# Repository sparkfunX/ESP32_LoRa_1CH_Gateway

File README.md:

SparkX ESP32 LoRa Single-Channel Gateway
========================================

This repo is the original SparkX version. Please see the [SparkFun repo](https://github.com/sparkfun/ESP32_LoRa_1Ch_Gateway/) for the latest and greatest.

[*SparkX  ESP32 LoRa Single-Channel Gateway (SPX-14893)*](https://www.sparkfun.com/products/14893)

The SparkX ESP32 LoRa Single-Channel Gateway combines an ESP32 -- a programmable microcontroller featuring both WiFi and Bluetooth radios -- with an RFM95W LoRa transceiver to create a single-channel LoRa gateway. It's a perfect, low-cost tool for monitoring a dozen-or-so LoRa devices, and relaying their messages up to the cloud.

Complete with a [Qwiic connector](https://www.sparkfun.com/qwiic) and a breadboard-compatible array of ESP32 pin-breakouts, this board can can also serve as a general-purpose ESP32/RFM95W development platform. So, instead of using it as a LoRaWAN gateway, you can turn it into a **LoRa device**, and use the powerful ESP32 microcontroller to monitor sensors, host a web server, run a display or more.

These boards are a great way to begin dipping your toes into the world of LoRa and LoRaWAN. Not only can they be programmed as versatile single-channel gateway, but they can also be used as a LoRa device, or a general ESP32/RFM95W development board.

For more information, check out our [ESP32 LoRa 1-CH Gateway, LoRaWAN, and the Things Network](https://learn.sparkfun.com/tutorials/esp32-lora-1-ch-gateway-lorawan-and-the-things-network) tutorial, which explains how to set the board up, and get it connected to The Things Network.

SparkFun labored with love to create this code. Feel like supporting open source hardware? 
Buy a [breakout board](https://www.sparkfun.com/products/14893) from SparkFun!

Repository Contents
-------------------

* **/Documents** - Datasheets
* **/Hardware** - Eagle design files (.brd, .sch)
* **/Firmware** - Example code and esp32-Arduino board files

License Information
-------------------

This product is _**open source**_! 

If you have any questions or concerns on licensing, please contact techsupport@sparkfun.com.

Please use, reuse, and modify these files as you see fit. Please maintain attribution to SparkFun Electronics and release any derivative under the same license.

Distributed as-is; no warranty is given.

- Your friends at SparkFun.

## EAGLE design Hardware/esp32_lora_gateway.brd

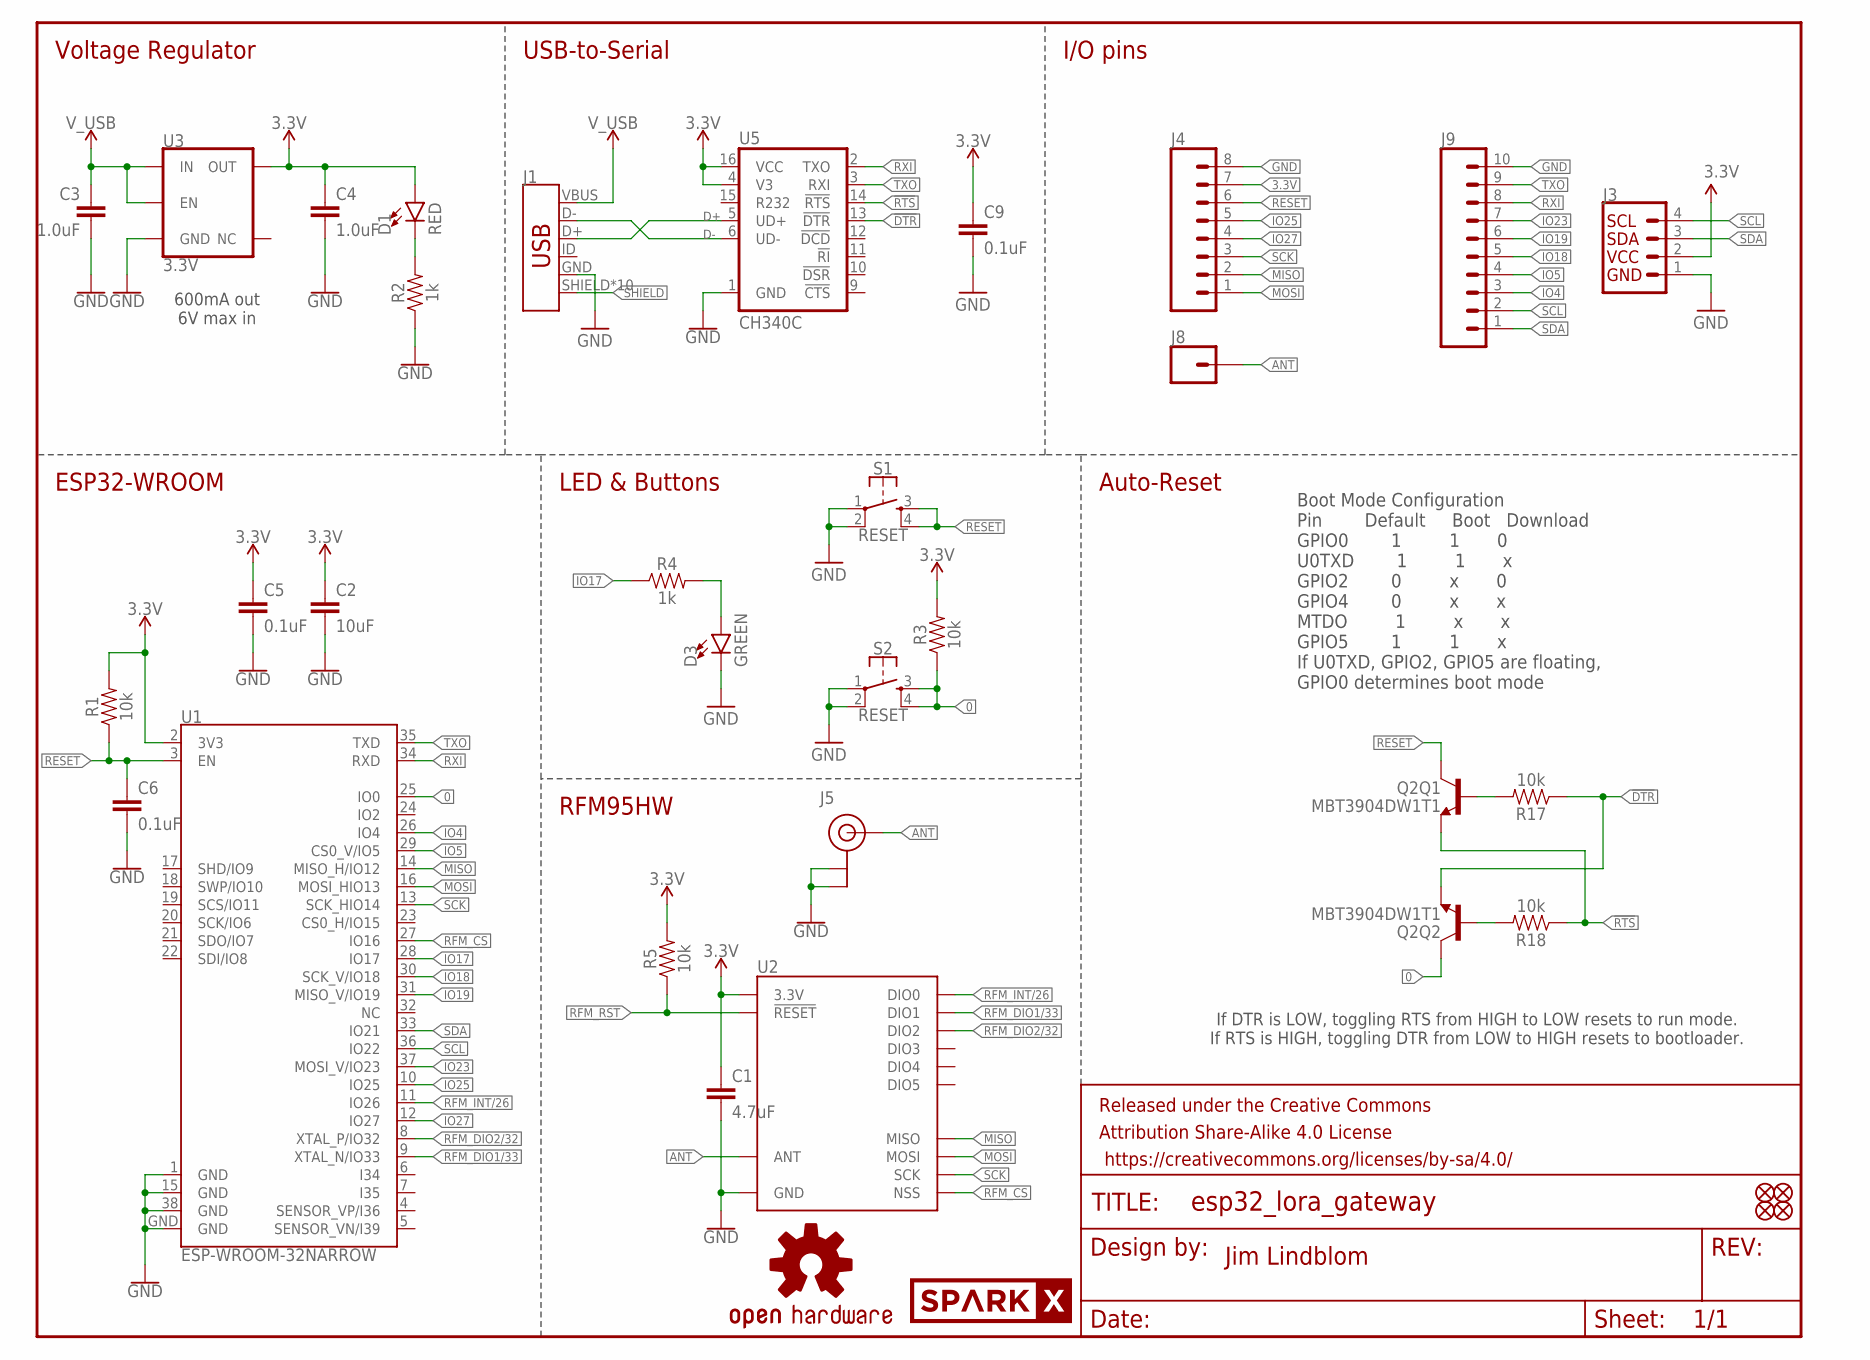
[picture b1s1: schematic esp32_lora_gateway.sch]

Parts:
C1: 4.7uF; 0603
C2: 10uF; 0603
C3, C4: 1.0uF; 0603
C5, C6: 0.1uF; 0603
C9: 0.1uF; 0603-CAP
D1: RED; LED-0603
D3: GREEN; LED-0603
FD1, FD2, FD3, FD4: FIDUCIALUFIDUCIAL; FIDUCIAL-MICRO
FRAME1: FRAME-LETTER; CREATIVE_COMMONS
J1: USB_MICRO-B_HALF_PTH_MILL; USB-MICROB-PTH-MILL
J3: QWIIC_CONNECTORJS-1MM; 1X04_1MM_RA
J4: CONN_08NO_SILK_FEMALE_PTH; 1X08_NO_SILK
J5: U.FL
J8: CONN_01PTH_NO_SILK_YES_STOP; 1X01_NO_SILK
J9: CONN_10NO_SILK_PTH_FEMALE; 1X10_NO_SILK
LOGO1: SPARKX-LOGO4; SPARKX-MEDIUM
LOGO2: OSHW-LOGOM; OSHW-LOGO-M
Q2: MBT3904DW1T1; SC70-6
R1, R3, R5, R17, R18: 10k; 0603
R2, R4: 1k; 0603
S1, S2: RESET; TACTILE_SWITCH_SMD_4.6X2.8MM
U1: ESP-WROOM-32NARROW; ESP-WROOM-32-NARROW
U2: RFM96W; RFM95/96/97/98W
U3: 3.3V; SOT23-5
U5: CH340C; SO016

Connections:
0: Q2.6 (C), R3.1, S2.3, S2.4, U1.25 (IO0)
3.3V: C1.1, C2.1, C4.1, C5.1, C9.1, D1.A, J3.2, J4.7, R1.2, R3.2, R5.2, U1.2 (3V3), U2.3.3V, U3.5 (OUT), U5.4 (V3), U5.16 (VCC)
!DTR: Q2.1 (E), R17.1, U5.13 (!DTR)
!RTS: Q2.4 (E), R18.1, U5.14 (!RTS)
ANT: J5.FEED (SIGNAL), J8.1, U2.ANT
D+: J1.D+, U5.5 (UD+)
D-: J1.D-, U5.6 (UD-)
GND: C1.2, C2.2, C3.2, C4.2, C5.2, C6.2, C9.2, D3.C, J1.GND, J3.1, J4.8, J5.1 (GND), J5.2 (GND), J9.10, R2.1, S1.1, S1.2, S2.1, S2.2, U1.1 (GND), U1.15 (GND), U1.38 (GND), U1.GND, U2.GND@1 (GND), U2.GND@2 (GND), U2.GND@3 (GND), U3.2 (GND), U5.1 (GND)
IO4: J9.3, U1.26 (IO4)
IO5: J9.4, U1.29 (CS0_V/IO5)
IO17: R4.1, U1.28 (IO17)
IO18: J9.5, U1.30 (SCK_V/IO18)
IO19: J9.6, U1.31 (MISO_V/IO19)
IO23: J9.7, U1.37 (MOSI_V/IO23)
IO25: J4.5, U1.10 (IO25)
IO27: J4.4, U1.12 (IO27)
MISO: J4.2, U1.14 (MISO_H/IO12), U2.MISO
MOSI: J4.1, U1.16 (MOSI_HIO13), U2.MOSI
unnamed: D1.C, R2.2
unnamed: D3.A, R4.2
unnamed: Q2.5 (B), R17.2
unnamed: Q2.2 (B), R18.2
RESET: C6.1, J4.6, Q2.3 (C), R1.1, S1.3, S1.4, U1.3 (EN)
RFM_CS: U1.27 (IO16), U2.NSS
RFM_DIO1/33: U1.9 (XTAL_N/IO33), U2.DIO1
RFM_DIO2/32: U1.8 (XTAL_P/IO32), U2.DIO2
RFM_INT/26: U1.11 (IO26), U2.DIO0
RFM_RST: R5.1, U2.!RESET
RXI: J9.8, U1.34 (RXD), U5.2 (TXO)
SCK: J4.3, U1.13 (SCK_HIO14), U2.SCK
SCL: J3.4, J9.2, U1.36 (IO22)
SDA: J3.3, J9.1, U1.33 (IO21)
SHIELD: J1.SHIELD, J1.SHIELD2 (SHIELD), J1.SHIELD3 (SHIELD), J1.SHIELD4 (SHIELD), J1.SHIELD5 (SHIELD), J1.SHIELD6 (SHIELD), J1.SHIELD7 (SHIELD), J1.SHIELD8 (SHIELD), J1.SHIELD9 (SHIELD), J1.SHIELD10 (SHIELD)
TXO: J9.9, U1.35 (TXD), U5.3 (RXI)
V_USB: C3.1, J1.VBUS, U3.1 (IN), U3.3 (EN)

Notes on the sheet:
Boot Mode Configuration Pin Default Boot Download GPIO0 1 1 0 U0TXD 1 1 x GPIO2 0 x 0 GPIO4 0 x x MTDO 1 x x GPIO5 1 1 x If U0TXD, GPIO2, GPIO5 are floating, GPIO0 determines boot mode
If DTR is LOW, toggling RTS from HIGH to LOW resets to run mode. If RTS is HIGH, toggling DTR from LOW to HIGH resets to bootloader.
600mA out 6V max in
Voltage Regulator
USB-to-Serial
I/O pins
ESP32-WROOM
LED & Buttons
Auto-Reset
RFM95HW
Jim Lindblom

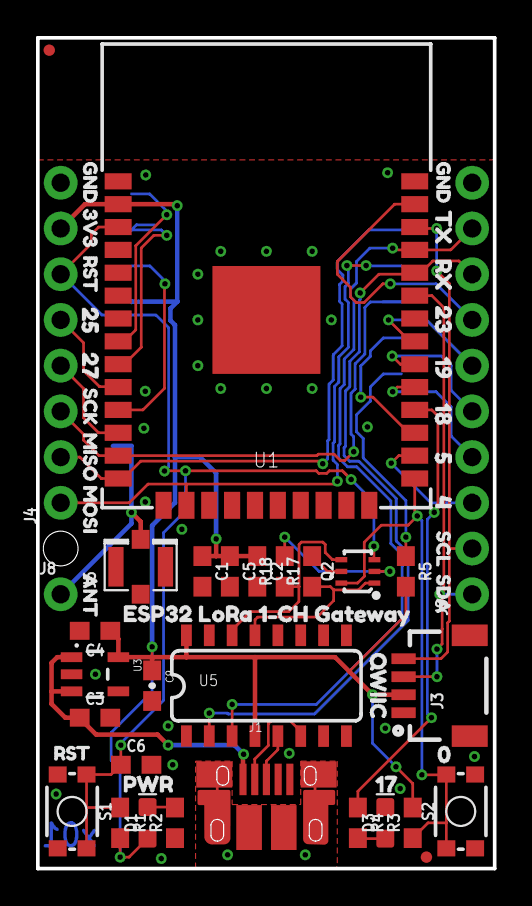
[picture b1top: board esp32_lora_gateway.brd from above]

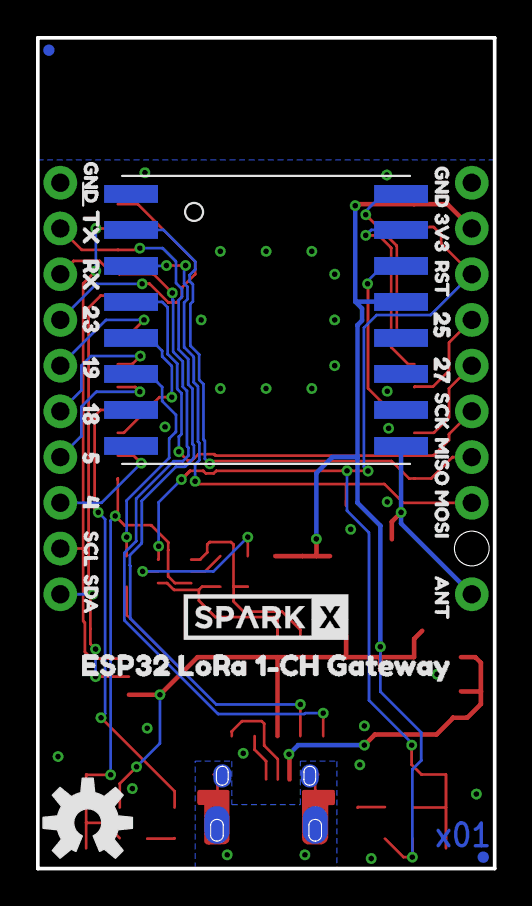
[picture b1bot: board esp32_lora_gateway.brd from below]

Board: 2 copper layers, 25.4 x 46.2 mm, 81 parts (25 on the bottom side), 35 nets.

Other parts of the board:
U$1, U$10, U$26, U$37: GND0
U$2, U$38: 3V31
U$3, U$20, U$39: RST2
U$4, U$40: 2517
U$5, U$41: 279
U$6, U$42: SCK3
U$7, U$43: MISO4
U$8, U$44: MOSI5
U$9, U$36: ANT6
U$11, U$27: TX16
U$12, U$28: RX15
U$13, U$29: 2314
U$14, U$30: 1912
U$15, U$31: 1811
U$16, U$32: 513
U$17, U$33: 410
U$18, U$34: SCL8
U$19, U$35: SDA7
U$21: 020
U$22: PWR19
U$23: 1722
U$24: QWIIC18
U$25: ESP32_LORA_1#CH_GATEWAY21
U$45: ESP32_LORA_1#CH_GATEWAY23

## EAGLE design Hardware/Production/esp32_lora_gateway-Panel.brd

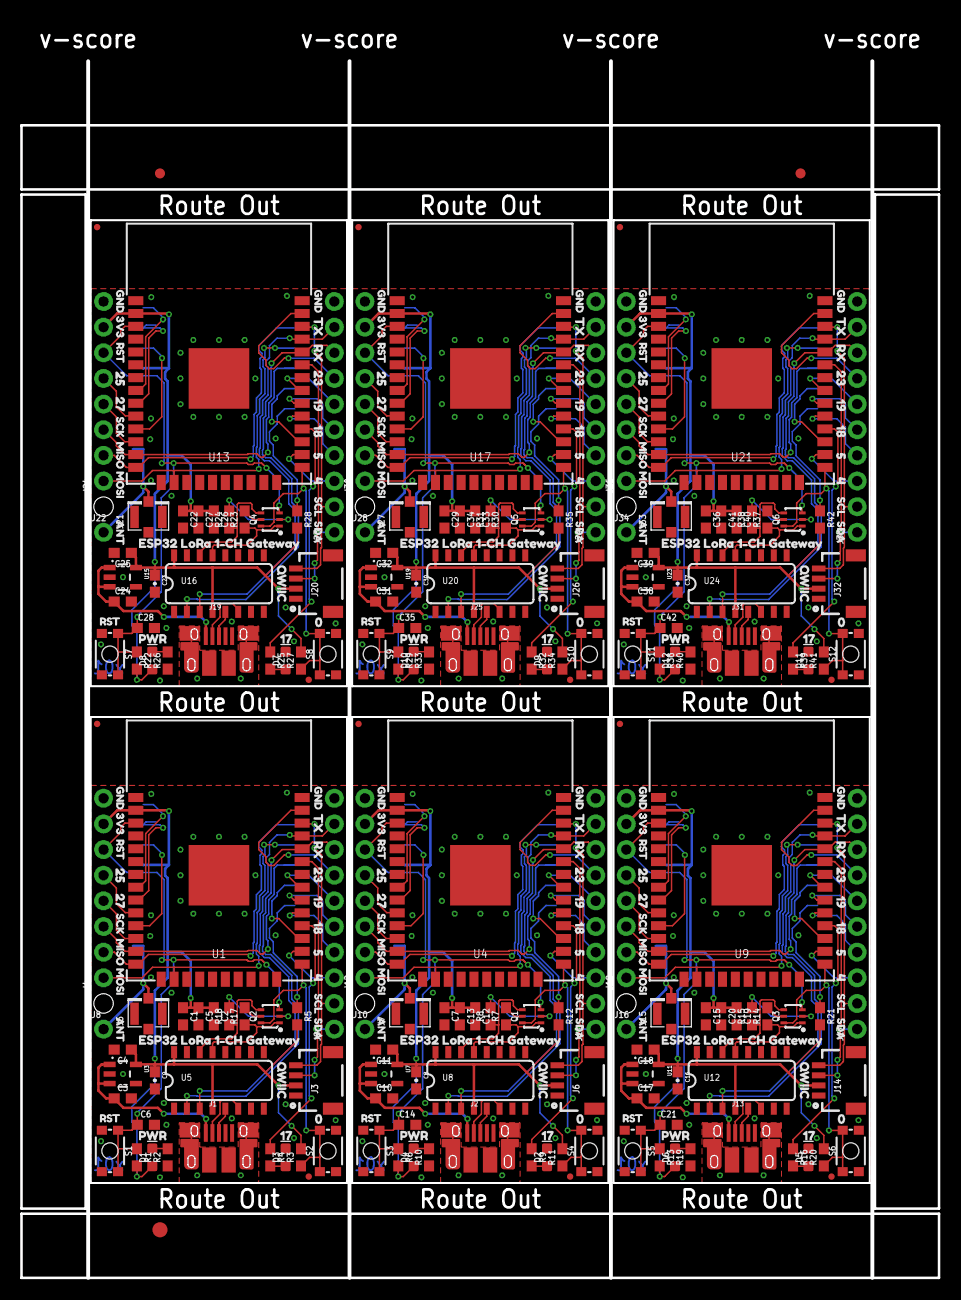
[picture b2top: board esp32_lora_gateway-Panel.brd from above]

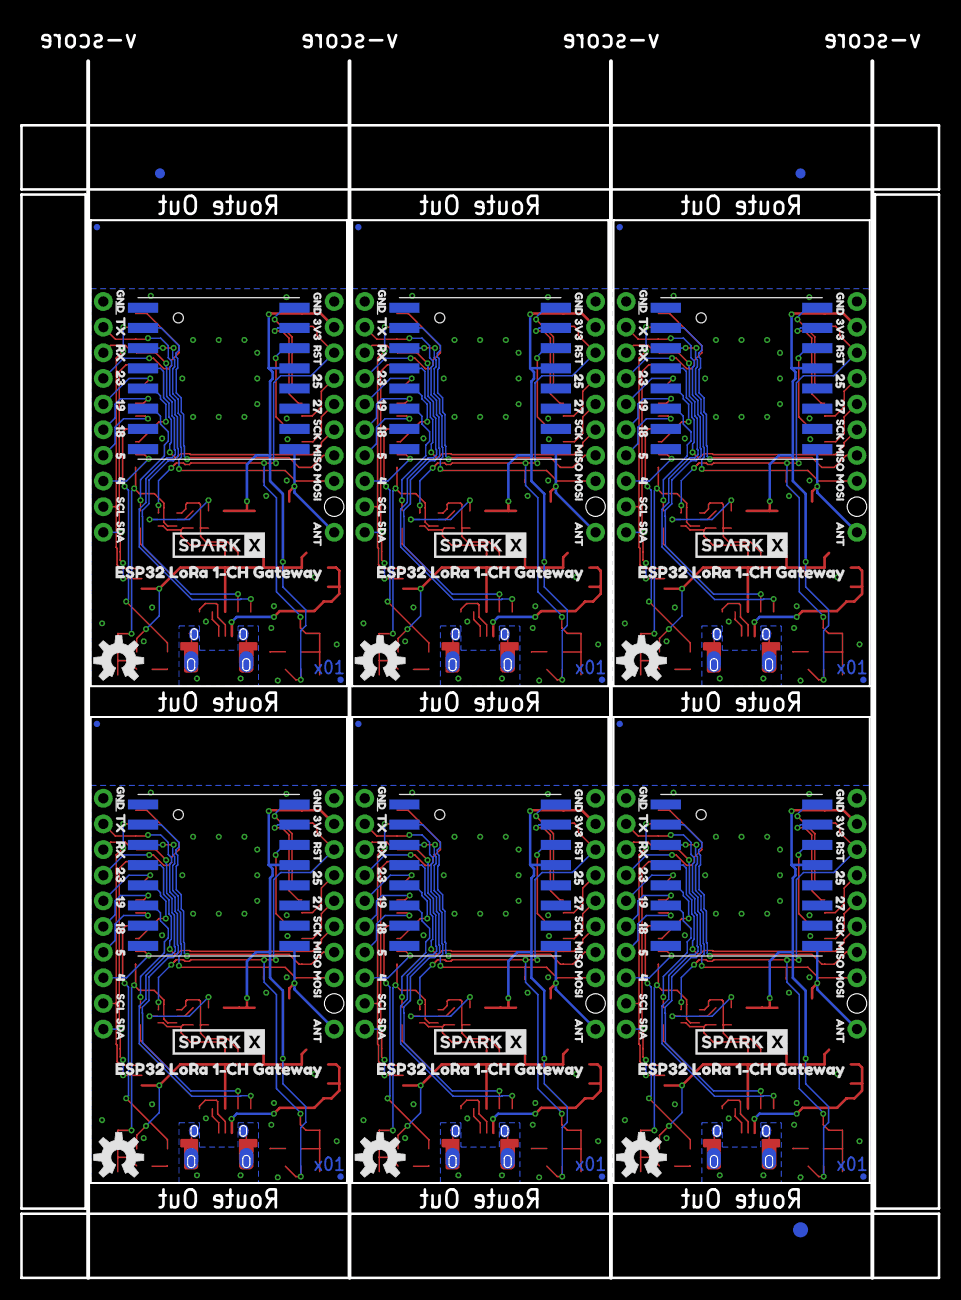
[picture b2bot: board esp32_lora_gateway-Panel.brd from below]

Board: 2 copper layers, 90.9 x 120.5 mm, 486 parts (153 on the bottom side), 210 nets.

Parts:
C1, C7, C15, C22, C29, C36: 4.7uF; 0603
C2, C12, C19, C26, C33, C40: 10uF; 0603
C3, C4, C10, C11, C17, C18, C24, C25, C31, C32, C38, C39: 1.0uF; 0603
C5, C6, C13, C14, C20, C21, C27, C28, C34, C35, C41, C42: 0.1uF; 0603
C8, C9, C16, C23, C30, C37: 0.1uF; 0603-CAP
D1, D4, D6, D8, D10, D12: RED; LED-0603
D2, D3, D5, D7, D9, D11: BLUE; LED-0603
E$1, E$2, E$3, E$4: FIDUCIAL-1X2
E$5, E$6: FIDUCIAL-1.5X3
FD1, FD2, FD3, FD4, FD5, FD6, FD7, FD8, FD9, FD10, FD11, FD12, FD13, FD14, FD15, FD16, FD17, FD18, FD19, FD20, FD21, FD22, FD23, FD24: FIDUCIALUFIDUCIAL; FIDUCIAL-MICRO
J1, J2, J13, J19, J25, J31: USB-MICROB-PTH-MILL
J3, J6, J14, J20, J26, J32: 1X04_1MM_RA
J4, J12, J18, J24, J30, J36: 1X08_NO_SILK
J5, J7, J15, J21, J27, J33: U.FL
J8, J10, J16, J22, J28, J34: 1X01_NO_SILK
J9, J11, J17, J23, J29, J35: 1X10_NO_SILK
LOGO1, LOGO3, LOGO5, LOGO7, LOGO9, LOGO11: SPARKX-LOGO4; SPARKX-MEDIUM
LOGO2, LOGO4, LOGO6, LOGO8, LOGO10, LOGO12: OSHW-LOGOM; OSHW-LOGO-M
Q1, Q2, Q3, Q4, Q5, Q6: MBT3904DW1T1; SC70-6
R1, R3, R5, R6, R7, R8, R11, R12, R13, R14, R15, R17, R18, R20, R21, R22, R23, R24, R27, R28, R29, R30, R31, R34, R35, R36, R37, R38, R41, R42: 10k; 0603
R2, R4, R9, R10, R16, R19, R25, R26, R32, R33, R39, R40: 1k; 0603
S1, S2, S3, S4, S5, S6, S7, S8, S9, S10, S11, S12: RESET; TACTILE_SWITCH_SMD_4.6X2.8MM
U1, U4, U9, U13, U17, U21: ESP-WROOM-32NARROW; ESP-WROOM-32-NARROW
U2, U6, U10, U14, U18, U22: RFM96W; RFM95/96/97/98W
U3, U7, U11, U15, U19, U23: 3.3V; SOT23-5
U5, U8, U12, U16, U20, U24: CH340C; SO016
U$1, U$10, U$26, U$37, U$47, U$55, U$71, U$82, U$92, U$100, U$116, U$127, U$137, U$145, U$161, U$172, U$182, U$190, U$206, U$217, U$227, U$235, U$251, U$262: GND0
U$2, U$38, U$48, U$83, U$93, U$128, U$138, U$173, U$183, U$218, U$228, U$263: 3V31
U$3, U$20, U$39, U$49, U$65, U$84, U$94, U$110, U$129, U$139, U$155, U$174, U$184, U$200, U$219, U$229, U$245, U$264: RST2
U$4, U$40, U$50, U$85, U$95, U$130, U$140, U$175, U$185, U$220, U$230, U$265: 2517
U$5, U$41, U$51, U$86, U$96, U$131, U$141, U$176, U$186, U$221, U$231, U$266: 279
U$6, U$42, U$52, U$87, U$97, U$132, U$142, U$177, U$187, U$222, U$232, U$267: SCK3
U$7, U$43, U$53, U$88, U$98, U$133, U$143, U$178, U$188, U$223, U$233, U$268: MISO4
U$8, U$44, U$54, U$89, U$99, U$134, U$144, U$179, U$189, U$224, U$234, U$269: MOSI5
U$9, U$36, U$46, U$81, U$91, U$126, U$136, U$171, U$181, U$216, U$226, U$261: ANT6
U$11, U$27, U$56, U$72, U$101, U$117, U$146, U$162, U$191, U$207, U$236, U$252: TX16
U$12, U$28, U$57, U$73, U$102, U$118, U$147, U$163, U$192, U$208, U$237, U$253: RX15
U$13, U$29, U$58, U$74, U$103, U$119, U$148, U$164, U$193, U$209, U$238, U$254: 2314
U$14, U$30, U$59, U$75, U$104, U$120, U$149, U$165, U$194, U$210, U$239, U$255: 1912
U$15, U$31, U$60, U$76, U$105, U$121, U$150, U$166, U$195, U$211, U$240, U$256: 1811
U$16, U$32, U$61, U$77, U$106, U$122, U$151, U$167, U$196, U$212, U$241, U$257: 513
U$17, U$33, U$62, U$78, U$107, U$123, U$152, U$168, U$197, U$213, U$242, U$258: 410
U$18, U$34, U$63, U$79, U$108, U$124, U$153, U$169, U$198, U$214, U$243, U$259: SCL8
U$19, U$35, U$64, U$80, U$109, U$125, U$154, U$170, U$199, U$215, U$244, U$260: SDA7
U$21, U$66, U$111, U$156, U$201, U$246: 020
U$22, U$67, U$112, U$157, U$202, U$247: PWR19
U$23, U$68, U$113, U$158, U$203, U$248: 1722
U$24, U$69, U$114, U$159, U$204, U$249: QWIIC18
U$25, U$70, U$115, U$160, U$205, U$250: ESP32_LORA_1#CH_GATEWAY21
U$45, U$90, U$135, U$180, U$225, U$270: ESP32_LORA_1#CH_GATEWAY23

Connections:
0: Q2.6, R3.1, S2.3, S2.4, U1.25
1: Q1.6, R11.1, S4.3, S4.4, U4.25
2: Q3.6, R20.1, S6.3, S6.4, U9.25
3: Q4.6, R27.1, S8.3, S8.4, U13.25
3.3V: C1.1, C2.1, C4.1, C5.1, C9.1, D1.A, J3.2, J4.7, R1.2, R3.2, R5.2, U1.2, U2.3.3V, U3.5, U5.4, U5.16
3.3V1: C7.1, C8.1, C11.1, C12.1, C13.1, D4.A, J6.2, J12.7, R6.2, R11.2, R12.2, U4.2, U6.3.3V, U7.5, U8.4, U8.16
3.3V2: C15.1, C16.1, C18.1, C19.1, C20.1, D6.A, J14.2, J18.7, R13.2, R20.2, R21.2, U9.2, U10.3.3V, U11.5, U12.4, U12.16
3.3V3: C22.1, C23.1, C25.1, C26.1, C27.1, D8.A, J20.2, J24.7, R22.2, R27.2, R28.2, U13.2, U14.3.3V, U15.5, U16.4, U16.16
3.3V4: C29.1, C30.1, C32.1, C33.1, C34.1, D10.A, J26.2, J30.7, R29.2, R34.2, R35.2, U17.2, U18.3.3V, U19.5, U20.4, U20.16
3.3V5: C36.1, C37.1, C39.1, C40.1, C41.1, D12.A, J32.2, J36.7, R36.2, R41.2, R42.2, U21.2, U22.3.3V, U23.5, U24.4, U24.16
4: Q5.6, R34.1, S10.3, S10.4, U17.25
5: Q6.6, R41.1, S12.3, S12.4, U21.25
!DTR: Q2.1, R17.1, U5.13
!DTR1: Q1.1, R7.1, U8.13
!DTR2: Q3.1, R14.1, U12.13
!DTR3: Q4.1, R23.1, U16.13
!DTR4: Q5.1, R30.1, U20.13
!DTR5: Q6.1, R37.1, U24.13
!RTS: Q2.4, R18.1, U5.14
!RTS1: Q1.4, R8.1, U8.14
!RTS2: Q3.4, R15.1, U12.14
!RTS3: Q4.4, R24.1, U16.14
!RTS4: Q5.4, R31.1, U20.14
!RTS5: Q6.4, R38.1, U24.14
ANT: J5.FEED, J8.1, U2.ANT
ANT1: J7.FEED, J10.1, U6.ANT
ANT2: J15.FEED, J16.1, U10.ANT
ANT3: J21.FEED, J22.1, U14.ANT
ANT4: J27.FEED, J28.1, U18.ANT
ANT5: J33.FEED, J34.1, U22.ANT
D+: J1.D+, U5.5
D+1: J2.D+, U8.5
D+2: J13.D+, U12.5
D+3: J19.D+, U16.5
D+4: J25.D+, U20.5
D+5: J31.D+, U24.5
D-: J1.D-, U5.6
D-1: J2.D-, U8.6
D-2: J13.D-, U12.6
D-3: J19.D-, U16.6
D-4: J25.D-, U20.6
D-5: J31.D-, U24.6
GND: C1.2, C2.2, C3.2, C4.2, C5.2, C6.2, C9.2, D3.C, J1.GND, J3.1, J4.8, J5.1, J5.2, J9.10, R2.1, S1.1, S1.2, S2.1, S2.2, U1.1, U1.15, U1.38, U1.GND, U2.GND@1, U2.GND@2, U2.GND@3, U3.2, U5.1
GND1: C7.2, C8.2, C10.2, C11.2, C12.2, C13.2, C14.2, D2.C, J2.GND, J6.1, J7.1, J7.2, J11.10, J12.8, R10.1, S3.1, S3.2, S4.1, S4.2, U4.1, U4.15, U4.38, U4.GND, U6.GND@1, U6.GND@2, U6.GND@3, U7.2, U8.1
GND2: C15.2, C16.2, C17.2, C18.2, C19.2, C20.2, C21.2, D5.C, J13.GND, J14.1, J15.1, J15.2, J17.10, J18.8, R19.1, S5.1, S5.2, S6.1, S6.2, U9.1, U9.15, U9.38, U9.GND, U10.GND@1, U10.GND@2, U10.GND@3, U11.2, U12.1
GND3: C22.2, C23.2, C24.2, C25.2, C26.2, C27.2, C28.2, D7.C, J19.GND, J20.1, J21.1, J21.2, J23.10, J24.8, R26.1, S7.1, S7.2, S8.1, S8.2, U13.1, U13.15, U13.38, U13.GND, U14.GND@1, U14.GND@2, U14.GND@3, U15.2, U16.1
GND4: C29.2, C30.2, C31.2, C32.2, C33.2, C34.2, C35.2, D9.C, J25.GND, J26.1, J27.1, J27.2, J29.10, J30.8, R33.1, S9.1, S9.2, S10.1, S10.2, U17.1, U17.15, U17.38, U17.GND, U18.GND@1, U18.GND@2, U18.GND@3, U19.2, U20.1
GND5: C36.2, C37.2, C38.2, C39.2, C40.2, C41.2, C42.2, D11.C, J31.GND, J32.1, J33.1, J33.2, J35.10, J36.8, R40.1, S11.1, S11.2, S12.1, S12.2, U21.1, U21.15, U21.38, U21.GND, U22.GND@1, U22.GND@2, U22.GND@3, U23.2, U24.1
IO1: J12.5, U4.10
IO2: J12.4, U4.12
IO3: J11.6, U4.31
IO4: J9.3, U1.26
IO5: J9.4, U1.29
IO6: J11.5, U4.30
IO7: J11.4, U4.29
IO8: J11.7, U4.37
IO9: J11.3, U4.26
IO10: R9.1, U4.28
IO11: J18.5, U9.10
IO12: J18.4, U9.12
IO13: J17.6, U9.31
IO14: J17.5, U9.30
IO15: J17.4, U9.29
IO16: J17.7, U9.37
IO17: R4.1, U1.28
IO18: J9.5, U1.30
IO19: J9.6, U1.31
IO20: J17.3, U9.26
IO21: R16.1, U9.28
IO22: J24.5, U13.10
IO23: J9.7, U1.37
IO24: J24.4, U13.12
IO25: J4.5, U1.10
IO26: J23.6, U13.31
IO27: J4.4, U1.12
IO28: J23.5, U13.30
IO29: J23.4, U13.29
IO30: J23.7, U13.37
IO31: J23.3, U13.26
IO32: R25.1, U13.28
IO33: J30.5, U17.10
IO34: J30.4, U17.12
IO35: J29.6, U17.31
IO36: J29.5, U17.30
IO37: J29.4, U17.29
IO38: J29.7, U17.37
IO39: J29.3, U17.26
IO40: R32.1, U17.28
IO41: J36.5, U21.10
IO42: J36.4, U21.12
IO43: J35.6, U21.31
IO44: J35.5, U21.30
IO45: J35.4, U21.29
IO46: J35.7, U21.37
IO47: J35.3, U21.26
IO48: R39.1, U21.28
MISO: J4.2, U1.14, U2.MISO
MISO1: J12.2, U4.14, U6.MISO
MISO2: J18.2, U9.14, U10.MISO
MISO3: J24.2, U13.14, U14.MISO
MISO4: J30.2, U17.14, U18.MISO
MISO5: J36.2, U21.14, U22.MISO
MOSI: J4.1, U1.16, U2.MOSI
MOSI1: J12.1, U4.16, U6.MOSI
MOSI2: J18.1, U9.16, U10.MOSI
MOSI3: J24.1, U13.16, U14.MOSI
MOSI4: J30.1, U17.16, U18.MOSI
MOSI5: J36.1, U21.16, U22.MOSI
unnamed: D1.C, R2.2
unnamed: D3.A, R4.2
unnamed: Q1.5, R7.2
unnamed: Q1.2, R8.2
unnamed: D2.A, R9.2
unnamed: D4.C, R10.2
unnamed: Q3.5, R14.2
unnamed: Q3.2, R15.2
unnamed: D5.A, R16.2
unnamed: Q2.5, R17.2
unnamed: D6.C, R19.2
unnamed: Q2.2, R18.2
unnamed: Q4.5, R23.2
unnamed: Q4.2, R24.2
unnamed: D7.A, R25.2
unnamed: D8.C, R26.2
unnamed: Q5.5, R30.2
unnamed: Q5.2, R31.2
unnamed: D9.A, R32.2
unnamed: D10.C, R33.2
unnamed: Q6.5, R37.2
unnamed: Q6.2, R38.2
unnamed: D11.A, R39.2
unnamed: D12.C, R40.2
RESET: C6.1, J4.6, Q2.3, R1.1, S1.3, S1.4, U1.3
RESET1: C14.1, J12.6, Q1.3, R6.1, S3.3, S3.4, U4.3
RESET2: C21.1, J18.6, Q3.3, R13.1, S5.3, S5.4, U9.3
RESET3: C28.1, J24.6, Q4.3, R22.1, S7.3, S7.4, U13.3
RESET4: C35.1, J30.6, Q5.3, R29.1, S9.3, S9.4, U17.3
RESET5: C42.1, J36.6, Q6.3, R36.1, S11.3, S11.4, U21.3
RFM_CS: U1.27, U2.NSS
RFM_CS1: U4.27, U6.NSS
RFM_CS2: U9.27, U10.NSS
RFM_CS3: U13.27, U14.NSS
RFM_CS4: U17.27, U18.NSS
RFM_CS5: U21.27, U22.NSS
RFM_DIO1/1: U4.9, U6.DIO1
RFM_DIO1/2: U9.9, U10.DIO1
RFM_DIO1/3: U13.9, U14.DIO1
RFM_DIO1/4: U17.9, U18.DIO1
RFM_DIO1/5: U21.9, U22.DIO1
RFM_DIO1/33: U1.9, U2.DIO1
RFM_DIO2/1: U4.8, U6.DIO2
RFM_DIO2/2: U9.8, U10.DIO2
RFM_DIO2/3: U13.8, U14.DIO2
RFM_DIO2/4: U17.8, U18.DIO2
RFM_DIO2/5: U21.8, U22.DIO2
RFM_DIO2/32: U1.8, U2.DIO2
RFM_INT/1: U4.11, U6.DIO0
RFM_INT/2: U9.11, U10.DIO0
RFM_INT/3: U13.11, U14.DIO0
RFM_INT/4: U17.11, U18.DIO0
RFM_INT/5: U21.11, U22.DIO0
RFM_INT/26: U1.11, U2.DIO0
RFM_RST: R5.1, U2.!RESET
RFM_RST1: R12.1, U6.!RESET
RFM_RST2: R21.1, U10.!RESET
RFM_RST3: R28.1, U14.!RESET
RFM_RST4: R35.1, U18.!RESET
RFM_RST5: R42.1, U22.!RESET
RXI: J9.8, U1.34, U5.2
RXI1: J11.8, U4.34, U8.2
RXI2: J17.8, U9.34, U12.2
RXI3: J23.8, U13.34, U16.2
RXI4: J29.8, U17.34, U20.2
RXI5: J35.8, U21.34, U24.2
SCK: J4.3, U1.13, U2.SCK
SCK1: J12.3, U4.13, U6.SCK
SCK2: J18.3, U9.13, U10.SCK
SCK3: J24.3, U13.13, U14.SCK
SCK4: J30.3, U17.13, U18.SCK
SCK5: J36.3, U21.13, U22.SCK
SCL: J3.4, J9.2, U1.36
SCL1: J6.4, J11.2, U4.36
SCL2: J14.4, J17.2, U9.36
SCL3: J20.4, J23.2, U13.36
SCL4: J26.4, J29.2, U17.36
SCL5: J32.4, J35.2, U21.36
SDA: J3.3, J9.1, U1.33
SDA1: J6.3, J11.1, U4.33
SDA2: J14.3, J17.1, U9.33
SDA3: J20.3, J23.1, U13.33
SDA4: J26.3, J29.1, U17.33
SDA5: J32.3, J35.1, U21.33
SHIELD: J1.SHIELD, J1.SHIELD2, J1.SHIELD3, J1.SHIELD4, J1.SHIELD5, J1.SHIELD6, J1.SHIELD7, J1.SHIELD8, J1.SHIELD9, J1.SHIELD10
SHIELD1: J2.SHIELD, J2.SHIELD2, J2.SHIELD3, J2.SHIELD4, J2.SHIELD5, J2.SHIELD6, J2.SHIELD7, J2.SHIELD8, J2.SHIELD9, J2.SHIELD10
SHIELD2: J13.SHIELD, J13.SHIELD2, J13.SHIELD3, J13.SHIELD4, J13.SHIELD5, J13.SHIELD6, J13.SHIELD7, J13.SHIELD8, J13.SHIELD9, J13.SHIELD10
SHIELD3: J19.SHIELD, J19.SHIELD2, J19.SHIELD3, J19.SHIELD4, J19.SHIELD5, J19.SHIELD6, J19.SHIELD7, J19.SHIELD8, J19.SHIELD9, J19.SHIELD10
SHIELD4: J25.SHIELD, J25.SHIELD2, J25.SHIELD3, J25.SHIELD4, J25.SHIELD5, J25.SHIELD6, J25.SHIELD7, J25.SHIELD8, J25.SHIELD9, J25.SHIELD10
SHIELD5: J31.SHIELD, J31.SHIELD2, J31.SHIELD3, J31.SHIELD4, J31.SHIELD5, J31.SHIELD6, J31.SHIELD7, J31.SHIELD8, J31.SHIELD9, J31.SHIELD10
TXO: J9.9, U1.35, U5.3
TXO1: J11.9, U4.35, U8.3
TXO2: J17.9, U9.35, U12.3
TXO3: J23.9, U13.35, U16.3
TXO4: J29.9, U17.35, U20.3
TXO5: J35.9, U21.35, U24.3
V_USB: C3.1, J1.VBUS, U3.1, U3.3
V_USB1: C10.1, J2.VBUS, U7.1, U7.3
V_USB2: C17.1, J13.VBUS, U11.1, U11.3
V_USB3: C24.1, J19.VBUS, U15.1, U15.3
V_USB4: C31.1, J25.VBUS, U19.1, U19.3
V_USB5: C38.1, J31.VBUS, U23.1, U23.3

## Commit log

2018-07-18 Hardware commit x01
2018-07-18 remove unused script'
2018-07-25 Changing blue LED to green.
2018-08-02 Moving part value text for assembly sheet. Set sch version.
2018-08-02 Add x01 schematic.
2018-08-02 Adding example device sketch and arduino-esp32 core files.
2018-08-02 Adding ESP32 and RFM95 documentation
2018-08-02 Adding product info to README
2018-08-14 Adding test firmware and batch file.
2018-10-24 Modifying and posting test code. Adding receiver test code.

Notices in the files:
parts and their libraries:
SparkFun-Capacitors: Licensing: Creative Commons ShareAlike 4.0 International - https://creativecommons.org/licenses/by-sa/4.0
SparkFun-Aesthetics: Released under the Creative Commons Attribution Share-Alike 4.0 License
SparkFun-Aesthetics: https://creativecommons.org/licenses/by-sa/4.0
